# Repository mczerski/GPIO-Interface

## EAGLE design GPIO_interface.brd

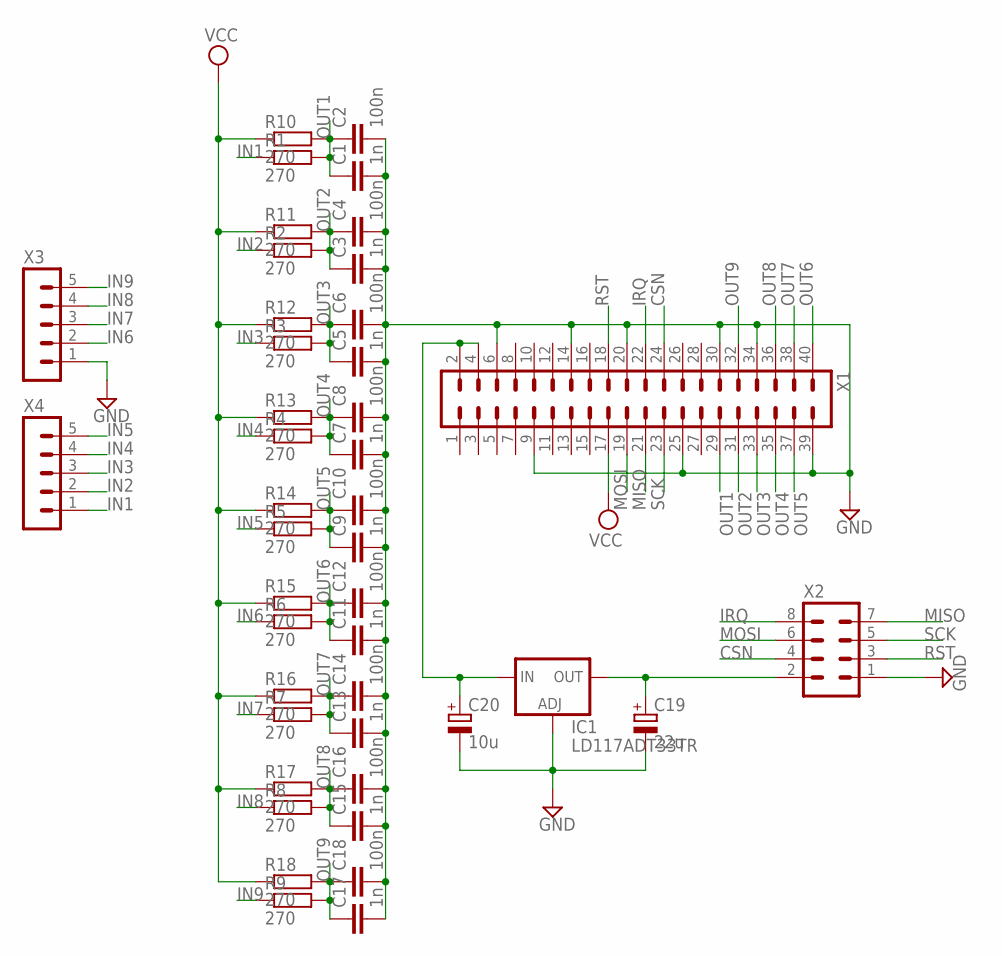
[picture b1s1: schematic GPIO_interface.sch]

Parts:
C1, C3, C5, C7, C9, C11, C13, C15, C17: 1n; C0603
C2, C4, C6, C8, C10, C12, C14, C16, C18: 100n; C0603
C19: 22u; C/6032-28R
C20: 10u; C/6032-28R
IC1: LD117ADT33TR; DPACK
R1, R2, R3, R4, R5, R6, R7, R8, R9, R10, R11, R12, R13, R14, R15, R16, R17, R18: 270; R0603
X1: MA20-2
X2: MA04-2
X3, X4: MA05-1

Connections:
CSN: X1.24, X2.4
GND: C1.2, C2.2, C3.2, C4.2, C5.2, C6.2, C7.2, C8.2, C9.2, C10.2, C11.2, C12.2, C13.2, C14.2, C15.2, C16.2, C17.2, C18.2, C19.-, C20.-, IC1.1 (ADJ), X1.6, X1.9, X1.14, X1.20, X1.25, X1.30, X1.34, X1.39, X2.1, X3.1
IN1: R1.1, X4.1
IN2: R2.1, X4.2
IN3: R3.1, X4.3
IN4: R4.1, X4.4
IN5: R5.1, X4.5
IN6: R6.1, X3.2
IN7: R7.1, X3.3
IN8: R8.1, X3.4
IN9: R9.1, X3.5
IRQ: X1.22, X2.8
MISO: X1.21, X2.7
MOSI: X1.19, X2.6
unnamed: C20.+, IC1.3 (IN), X1.2, X1.4
unnamed: C19.+, IC1.4 (OUT), X2.2
OUT1: C1.1, C2.1, R1.2, R10.2, X1.29
OUT2: C3.1, C4.1, R2.2, R11.2, X1.31
OUT3: C5.1, C6.1, R3.2, R12.2, X1.33
OUT4: C7.1, C8.1, R4.2, R13.2, X1.35
OUT5: C9.1, C10.1, R5.2, R14.2, X1.37
OUT6: C11.1, C12.1, R6.2, R15.2, X1.40
OUT7: C13.1, C14.1, R7.2, R16.2, X1.38
OUT8: C15.1, C16.1, R8.2, R17.2, X1.36
OUT9: C17.1, C18.1, R9.2, R18.2, X1.32
RST: X1.18, X2.3
SCK: X1.23, X2.5
VCC: R10.1, R11.1, R12.1, R13.1, R14.1, R15.1, R16.1, R17.1, R18.1, X1.17

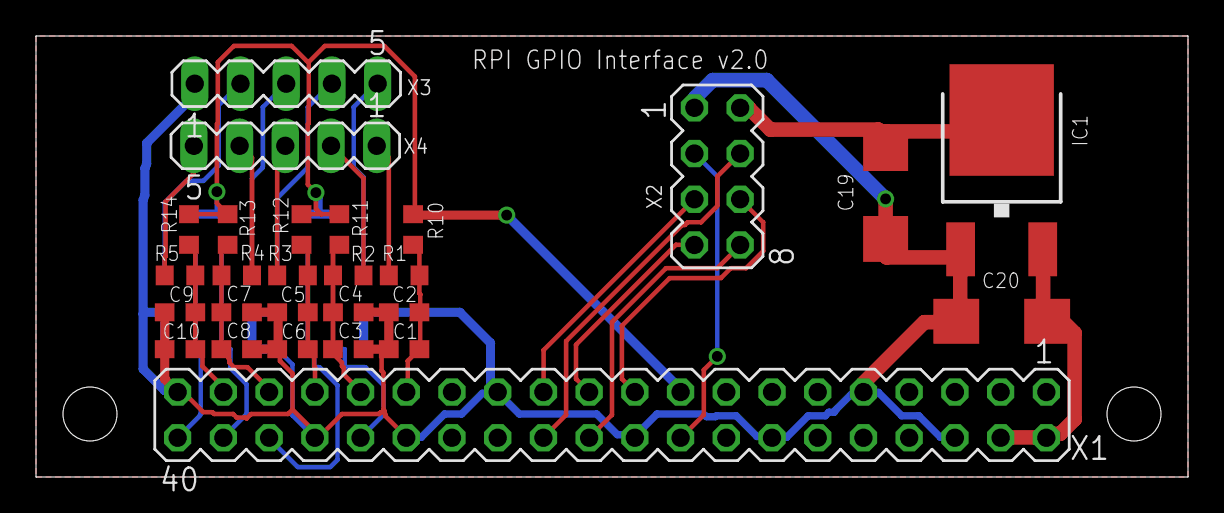
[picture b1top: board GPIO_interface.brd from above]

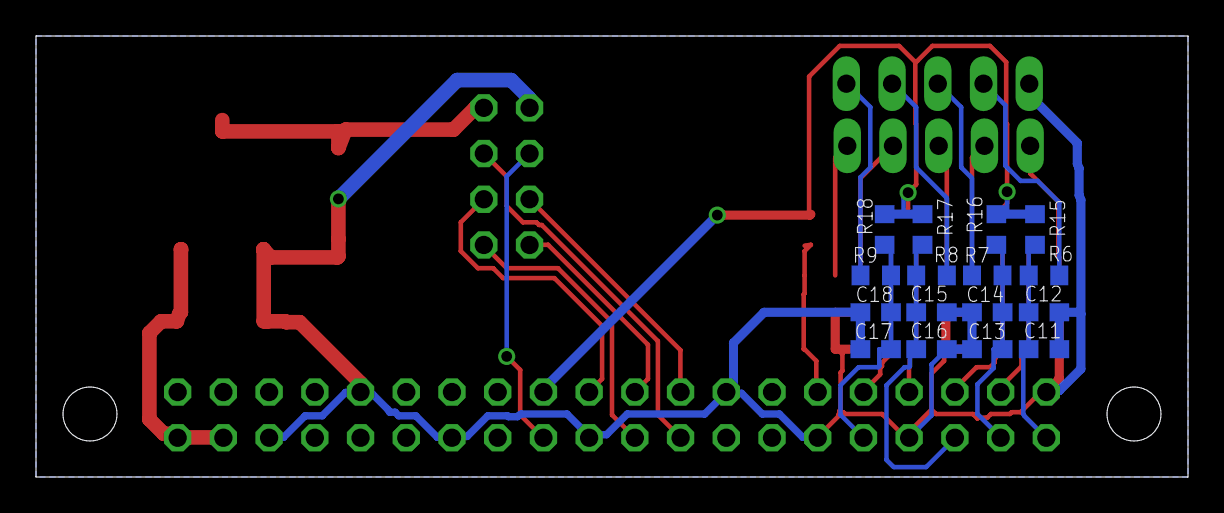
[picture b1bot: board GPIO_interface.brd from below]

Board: 2 copper layers, 64.0 x 24.5 mm, 43 parts (16 on the bottom side), 28 nets.

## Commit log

2017-06-18 wersja pod pcbs.io
2018-09-23 add LDO, use whole RPI connector
2018-09-23 cleanup names on pcb
2018-09-23 add name to pcb
